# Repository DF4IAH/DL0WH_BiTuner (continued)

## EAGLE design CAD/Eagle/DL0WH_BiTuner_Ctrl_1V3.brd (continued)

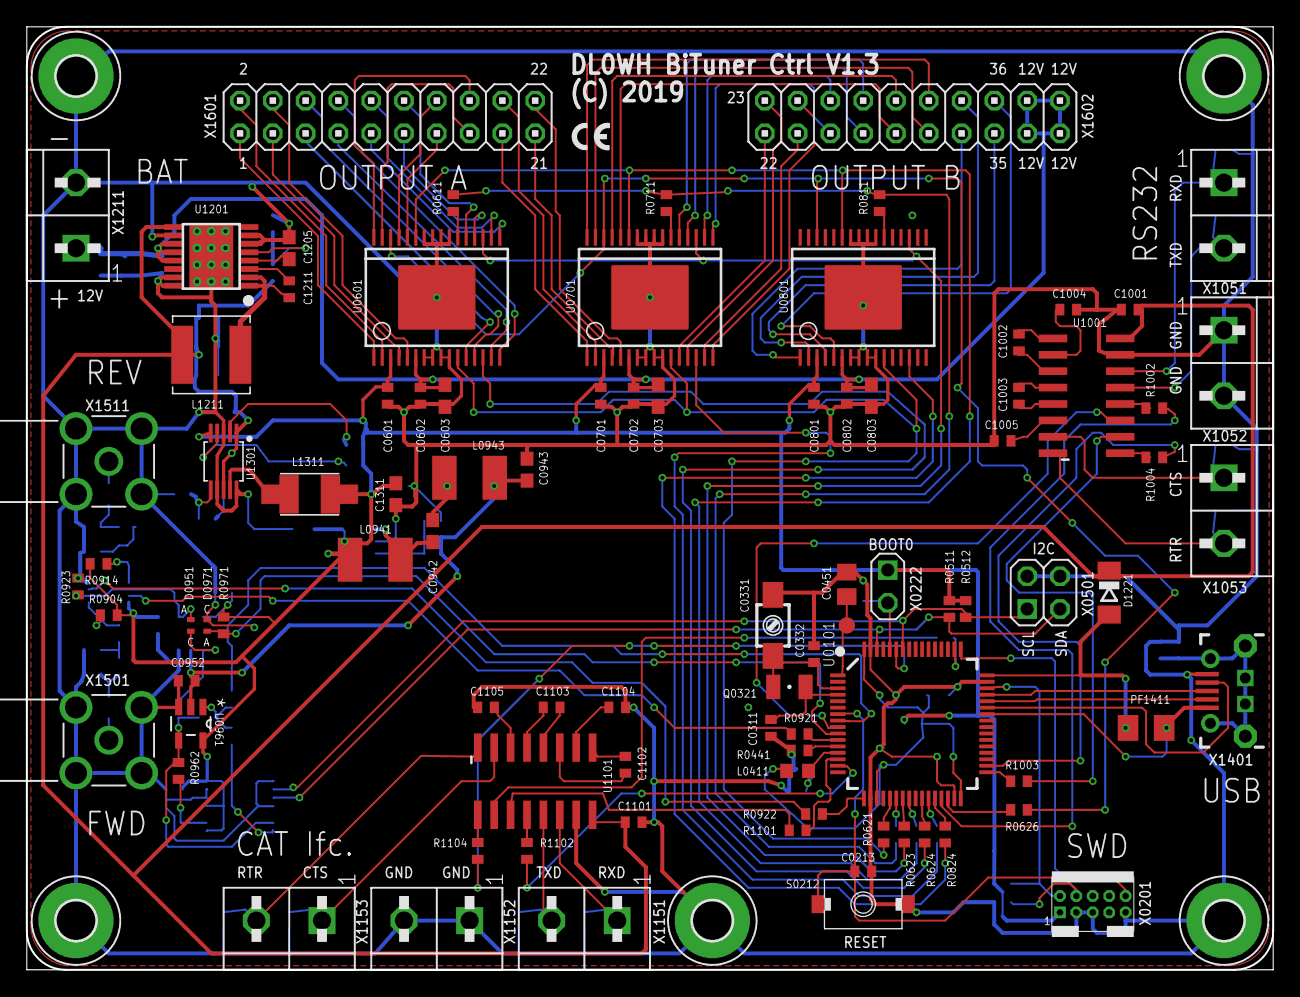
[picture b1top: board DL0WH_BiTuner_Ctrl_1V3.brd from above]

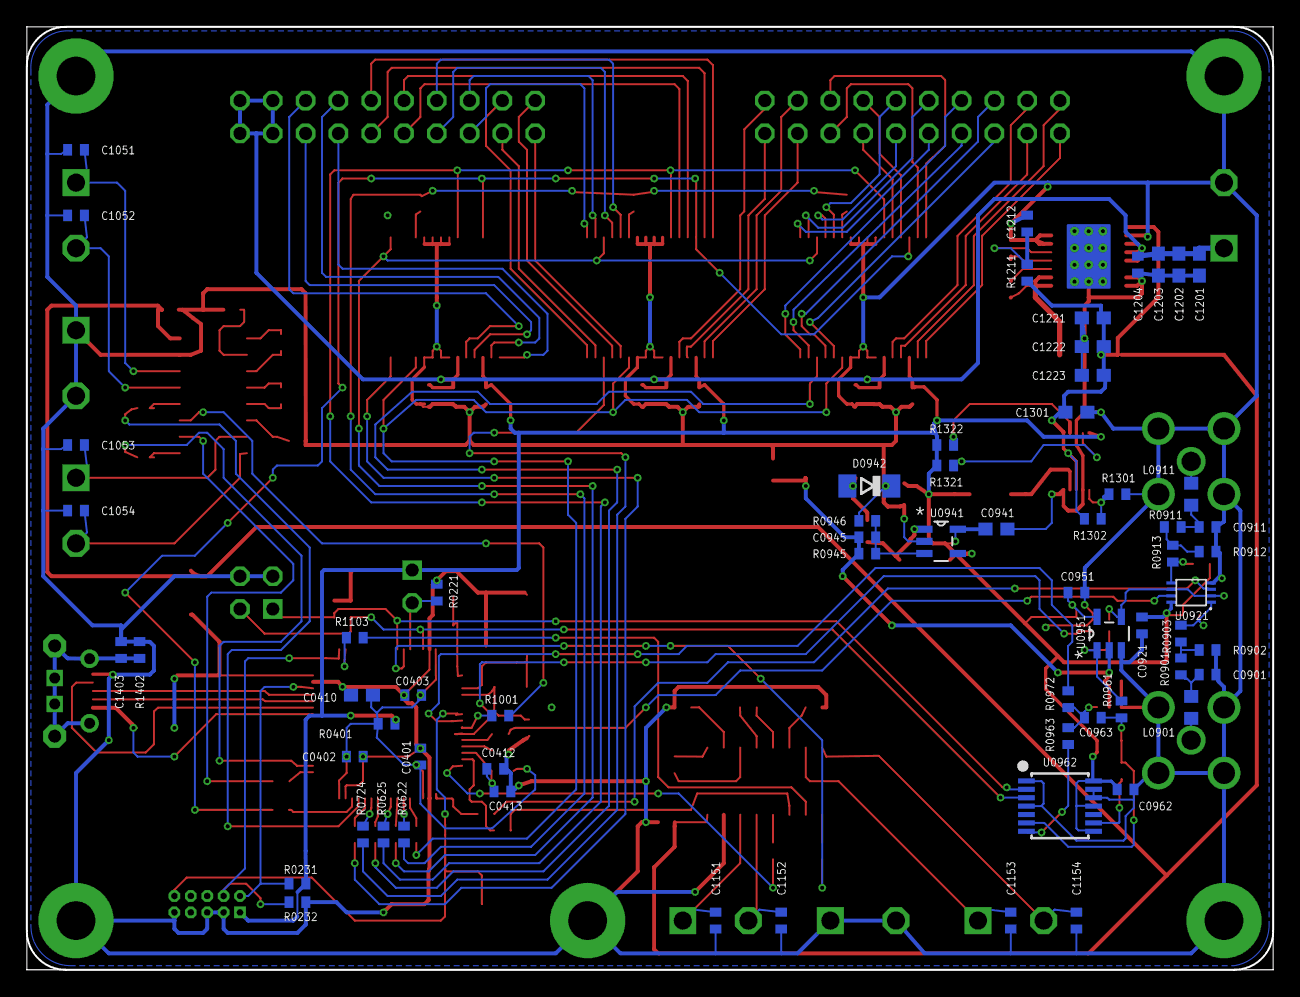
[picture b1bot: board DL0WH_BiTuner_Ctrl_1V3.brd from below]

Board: 2 copper layers, 96.5 x 73.0 mm, 160 parts (65 on the bottom side), 145 nets.

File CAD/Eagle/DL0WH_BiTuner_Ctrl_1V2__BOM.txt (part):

Stückliste exportiert aus /Users/espero/nfs_ds_nfs/git/_untracked/DL0WH_BiTuner/CAD/Eagle/DL0WH_BiTuner_Ctrl_1V2.sch am 19.04.19 14:24

Qty Value                    Device                               Package                             Parts                                                                                                                                             Description                                           

1   STM32L476RXT_64PIN_LDO   STM32L476RXT_64PIN_LDO               LQFP64                              U0101                                                                                                                                             STM32L476RxT 64LQFP                                   

2   MAX232_SOIC16            MAX232_SOIC16                        SOIC16N                             U1001, U1101                                                                                                                                      RS232 TRANSCEIVER                                     

1   LM53603-Q1               LM53603-Q1                           HTSSOP16                            U1201                                                                                                                                             TI LM53603-Q1                                         
1   TPS62056                 TPS62051                             S-PDSO-G10                          U1301                                                                                                                                             TPS62051 800-mA Synchronous Step-Down Converter: 3.3V 
1   LM2611                   LM2611                               SOT95P280X145-5N                    U0941                                                                                                                                             IC REG CUK INV ADJ 1.2A SOT23-5                       

2   OPA354                   OPA354                               SOT-23-5                            U0951, U0961                                                                                                                                      CMOS OPERATIONAL AMPLIFIERS                           

3   MC33996                  MC33996                              SOICW32                             U0601, U0701, U0801                                                                                                                               NXP MC33996                                           

1   TS5A23166                TS5A23166                            R-PDSO-G8                           U0921                                                                                                                                             TS5A23166                                             

1   MCP4661-103E-MS          MCP4661-104E-MS                      TSSOP14                             U0962                                                                                                                                             Microchip MCP4661                                     

1   ABS07-32.768KHZ          ABS07-32.768KHZ                      ABS07                               Q0321                                                                                                                                             ABRACON ABS07                                         

2   CMAD6001                 D_SOD923                             SOD923                              D0951, D0971                                                                                                                                      DIODE with SOD923 footprint                           
2   CRS08                    CRS08                                SOD80C                              D0942, D1221                                                                                                                                      SCHOTTKY BARRIER RECTIFIER                            


2   0R                       R-EU_R0402                           R0402                               R0441, R0622                                                                                                                                      RESISTOR, European symbol                             
1   3R                       R-EU_R0402                           R0402                               R1211                                                                                                                                             RESISTOR, European symbol                             
21  47R                      R-EU_R0402                           R0402                               R0611, R0621, R0623, R0624, R0625, R0626, R0711, R0724, R0811, R0824, R0921, R0922, R0972, R1001, R1002, R1003, R1004, R1101, R1102, R1103, R1104 RESISTOR, European symbol                             
6   1kR                      R-EU_R0402                           R0402                               R0511, R0512, R0901, R0911, R0961, R0962                                                                                                          RESISTOR, European symbol                             
2   2kR                      L-EUL0603                            L0603                               L0901, L0911                                                                                                                                      INDUCTOR, European symbol                             
1   8.2kR                    R-EU_R0402                           R0402                               R0945                                                                                                                                             RESISTOR, European symbol                             
1   10kR                     R-EU_R0402                           R0402                               R0971                                                                                                                                             RESISTOR, European symbol                             
2   15kR                     R-EU_R0402                           R0402                               R0902, R0912                                                                                                                                      RESISTOR, European symbol                             
1   20kR                     R-EU_R0402                           R0402                               R0963                                                                                                                                             RESISTOR, European symbol                             
2   33kR                     R-EU_R0402                           R0402                               R0221, R0946                                                                                                                                      RESISTOR, European symbol                             
1   100kR                    R-EU_R0402                           R0402                               R1301                                                                                                                                             RESISTOR, European symbol                             
2   150kR                    R-EU_R0402                           R0402                               R0903, R0913                                                                                                                                      RESISTOR, European symbol                             
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
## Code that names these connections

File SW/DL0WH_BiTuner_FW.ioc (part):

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Mcu.Name=STM32L476R(C-E-G)Tx
Mcu.Package=LQFP64
Mcu.UserName=STM32L476RGTx
PA0.GPIOParameters=GPIO_Speed
PA0.GPIO_Speed=GPIO_SPEED_FREQ_MEDIUM
PA0.Mode=Asynchronous
PA0.Signal=UART4_TX
PA1.GPIOParameters=GPIO_Speed,GPIO_PuPd
PA1.GPIO_PuPd=GPIO_PULLUP
PA1.GPIO_Speed=GPIO_SPEED_FREQ_MEDIUM
PA1.Mode=Asynchronous
PA1.Signal=UART4_RX
PA10.Mode=OTG/Dual_Role_Device
PA10.Signal=USB_OTG_FS_ID
PA11.Mode=OTG/Dual_Role_Device
PA11.Signal=USB_OTG_FS_DM
PA12.Mode=OTG/Dual_Role_Device
PA12.Signal=USB_OTG_FS_DP
PA13\ (JTMS-SWDIO).Signal=SYS_JTMS-SWDIO
PA14\ (JTCK-SWCLK).Signal=SYS_JTCK-SWCLK
PA15\ (JTDI).GPIOParameters=GPIO_Speed
PA15\ (JTDI).GPIO_Speed=GPIO_SPEED_FREQ_MEDIUM
PA15\ (JTDI).Mode=CTS_RTS
PA15\ (JTDI).Signal=UART4_RTS
PA2.Mode=SYS_WakeUp3
PA2.Signal=SYS_WKUP4
PA3.GPIOParameters=GPIO_Label
PA3.GPIO_Label=GPIO_SWR_SEL_REV
PA3.Signal=GPIO_Output
PA4.Signal=COMP_DAC11_group
PA5.Mode=Full_Duplex_Master
PA5.Signal=SPI1_SCK
PA6.GPIOParameters=GPIO_PuPd
PA6.GPIO_PuPd=GPIO_PULLDOWN
PA6.Mode=Full_Duplex_Master
PA6.Signal=SPI1_MISO
PA7.Mode=Full_Duplex_Master
PA7.Signal=SPI1_MOSI
PA8.Mode=Activate_SOF_FS
PA8.Signal=USB_OTG_FS_SOF
PA9.Mode=Activate_VBUS
PA9.Signal=USB_OTG_FS_VBUS
PB0.GPIOParameters=GPIO_Speed,PinState,GPIO_Label
PB0.GPIO_Label=GPIO_SPI_SEL_L
PB0.GPIO_Speed=GPIO_SPEED_FREQ_VERY_HIGH
PB0.PinState=GPIO_PIN_SET
PB0.Signal=GPIO_Output
PB1.GPIOParameters=GPIO_Speed,PinState,GPIO_Label
PB1.GPIO_Label=GPIO_SPI_SEL_C
PB1.GPIO_Speed=GPIO_SPEED_FREQ_VERY_HIGH
PB1.PinState=GPIO_PIN_SET
PB1.Signal=GPIO_Output
PB10.GPIOParameters=GPIO_Speed,GPIO_PuPd
PB10.GPIO_PuPd=GPIO_PULLUP
PB10.GPIO_Speed=GPIO_SPEED_FREQ_MEDIUM
PB10.Mode=Asynchronous
PB10.Signal=LPUART1_RX
PB11.GPIOParameters=GPIO_Label
PB11.GPIO_Label=GPIO_SPI_PWM
PB11.Signal=GPIO_Output
PB12.GPIOParameters=GPIO_Speed
PB12.GPIO_Speed=GPIO_SPEED_FREQ_MEDIUM
PB12.Mode=CTS_RTS
PB12.Signal=LPUART1_RTS
PB13.GPIOParameters=GPIO_Speed,GPIO_PuPd
PB13.GPIO_PuPd=GPIO_PULLUP
PB13.GPIO_Speed=GPIO_SPEED_FREQ_MEDIUM
PB13.Mode=CTS_RTS
PB13.Signal=LPUART1_CTS
PB2.GPIOParameters=GPIO_Speed,PinState,GPIO_Label
PB2.GPIO_Label=GPIO_SPI_SEL_EXT
PB2.GPIO_Speed=GPIO_SPEED_FREQ_VERY_HIGH
PB2.PinState=GPIO_PIN_SET
PB2.Signal=GPIO_Output
PB4\ (NJTRST).Mode=INP
PB4\ (NJTRST).Signal=COMP2_INP
PB6.Mode=I2C
PB6.Signal=I2C1_SCL
PB7.GPIOParameters=GPIO_Speed,GPIO_PuPd
PB7.GPIO_PuPd=GPIO_PULLUP
PB7.GPIO_Speed=GPIO_SPEED_FREQ_MEDIUM
PB7.Mode=CTS_RTS
PB7.Signal=UART4_CTS
PB9.Mode=I2C
PB9.Signal=I2C1_SDA
PC0.Signal=ADCx_IN1
PC1.GPIOParameters=GPIO_Speed
PC1.GPIO_Speed=GPIO_SPEED_FREQ_MEDIUM
PC1.Mode=Asynchronous
PC1.Signal=LPUART1_TX
PC13.Mode=Timestamp enabled
PC13.Signal=RTC_TS
PC14-OSC32_IN\ (PC14).Mode=LSE-External-Oscillator
PC14-OSC32_IN\ (PC14).Signal=RCC_OSC32_IN
PC15-OSC32_OUT\ (PC15).Mode=LSE-External-Oscillator
PC15-OSC32_OUT\ (PC15).Signal=RCC_OSC32_OUT
PC2.Signal=ADCx_IN3
PC3.GPIOParameters=GPIO_Label
PC3.GPIO_Label=GPIO_SWR_SEL_FWD
PC3.Signal=GPIO_Output
PC4.GPIOParameters=GPIO_Label
PC4.GPIO_Label=GPIO_SPI_RST
PC4.Signal=GPIO_Output
PC5.Mode=INP
PC5.Signal=COMP1_INP
PH0-OSC_IN\ (PH0).Mode=HSE-External-Oscillator
PH0-OSC_IN\ (PH0).Signal=RCC_OSC_IN
PH1-OSC_OUT\ (PH1).Mode=HSE-External-Oscillator
PH1-OSC_OUT\ (PH1).Signal=RCC_OSC_OUT
RCC.HSE_VALUE=8000000
RCC.SYSCLKFreq_VALUE=16000000
RCC.SYSCLKSource=RCC_SYSCLKSOURCE_HSI
board=custom

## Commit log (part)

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2018-12-13 README.md - explain intension of this modified FW
2018-12-13 Initial import of re-worked sources to compile with AtmelStudio 7
2018-12-13 Renaming of the sources to clearly disconnect from the DJ0ABR firmware
2018-12-13 .vs - is this directory important to include?
2018-12-29 Readout of DJ0ARB ATmega88 for security reasons (FLASH & EEPROM)
2018-12-29 No debug mode available - do not use SPI and debugWIRE together!
2018-12-30 Refactor project
2018-12-30 HW_1V0 - CAD/Eagle - Copy template from HFT-Core-Module
2018-12-30 HW_1V0 - CAD/Eagle - STM32L476RGT6 added to df4iah_stm32l4.lbr
2018-12-31 HW_1V0 - CAD/Eagle - I/O drivers added
2018-12-31 HW_1V0 - CAD/Eagle - level shifter not needed and removed
2018-12-31 HW_1V0 - CAD/Eagle - I2C port expander not needed and removed
2019-01-01 HW_1V0 - CAD/Eagle - I2C port added
2019-01-01 HW_1V0 - CAD/Eagle - SWR metering added, all placed
2019-01-01 DOCS - Datasheets and more docs added
2019-01-01 HW_1V0 - CAD/Eagle - prepared BOM and adjusted some package sizes - still L9011 needs correct package
2019-01-01 HW_1V0 - CAD/Eagle - pages renumbered: 17 pages
2019-01-02 SW - move _historic firmware to SW directory
2019-01-02 HW_1V0 - text size fixed for 0603 and 0402 devices
2019-01-02 HW_1V0 - CAD/Eagle - some parts re-routed
2019-01-02 HW_1V0 - CAD/Eagle - all placed, next: ERC and DRC
2019-01-02 HW_1V0 - CAD/Eagle - missing *.dru file added
2019-01-02 HW_1V0 - CAD/Eagle - some DRC error fixed
2019-01-02 DOCS - picture of V1.0 SW MCU Pinout added
2019-01-03 HW_1V0 - CAD/Eagle - I/O protection on V24 lines added
2019-01-04 DOCS - Final PCB picture upload
2019-01-04 HW_1V0 - CAD/Eagle - Ready for V1.0 production.
2019-01-04 HW_1V0 - CAD/Eagle - Pre-view pictures of the PCB added
2019-01-04 HW_1V0 - CAD/Eagle - Prepare for README.md update
2019-01-05 DOCS - Latching relays added
2019-01-05 SW - Initial software generation from STM32CubeMX
2019-01-05 SW - Some modifications in code generation done
2019-01-05 SW - FreeRTOS tasks and pipes established
2019-01-05 SW - some code taken from HFT-Core-Module main.[c|h]
2019-01-06 SW - infrastructure from HFT-Core-Module used as template
2019-01-06 SW - MCU ADC1..3 convertion added
2019-01-10 SW - _historic - old firmware for ATmega88 adapted to new build environment with additional mods, 9600 baud.
2019-01-11 DOCS - manufacturing - pre-views of top and bottom of the PCB
2019-01-12 SW - SPI communication added
2019-01-13 SW - SWR opti algo expanded
2019-01-13 SW - SWR opti algo missing parts added
2019-01-13 SW - Tester for task_Controller auto tuner Algo added
2019-01-13 SW - Tester expanded
2019-01-13 SW - task_Controller - missing prototypes added
2019-01-13 SW - tester - step size fixed
2019-01-14 SW - tuner Algo uses real capacity and inductivity values instead of L/C count numbers due to overlapping areas
2019-01-14 SW - printf() format fixes
2019-01-15 SW - print format different for STM32L4 and Linux/Mac environment
2019-01-15 SW - SWR Algo - additional state for FSM
2019-01-15 SW - SWR Algo - VSWR simulator added
2019-01-15 SW - SWR Algo - wrong signedness fixed
2019-01-15 SW - formatting
2019-01-15 SW - Tuner Algo - logging of proved code removed
2019-01-15 SW - Tuner Algo - first test run
2019-01-16 SW - Tuner Algo - improvements made
2019-01-17 SW - Tuner Algo - more modularized
2019-01-17 HW - CAD/Eagle/lbr - STM32L4 library with bad package LQFP64 fixed, LQFP144 minor fix
2019-01-17 SW - _Tests - more Algo checks
2019-01-17 HW_1V1 - CAD/Eagle - after DRC fixes, ready for production with new STM32L476 device package.
2019-01-18 SW - Tuner Algo - refactoring
2019-01-18 SW - Tuner Algo - Half strategy to work over
2019-01-19 SW - Tuner Algo - ZeroX okay, fine tuner under test
2019-01-19 SW - Tuner Algo - fine tuner needs better pre-placement
2019-01-19 SW - _Tests - some more tweaks done
2019-01-19 SW - _Tests - working for around 1:10 --> match
2019-01-19 SW - _Tests - Ground plane impedances added
2019-01-20 SW - verified AutoTuner coded included
2019-01-20 SW - task_Controller - Welcome message to the USB console added
2019-01-27 SW - Interpreter adapted
2019-01-27 SW - Help screen update
2019-01-28 SW - task_Controller - some more interactions
2019-01-28 SW - task_UART and task_CAT added
2019-01-29 SW - task_UART - adapted for current build
2019-01-29 SW - task_CAT - copied and adapted for current build
2019-01-29 SW - task_Interpreter - warning solved
2019-02-01 DOCS - 76_SWD-connector - added
2019-02-01 HW_1V2 - df4iah_connector.lbr - SWD connector fixed
2019-02-01 DOCS - README.md - new PCB screenshots added
2019-02-01 DOCS - README.md - tidy up
2019-02-01 DOCS - 32_PMIC - docs of both used PMICs added
2019-02-01 HW_1V1 - TPS62051 changed to TPS62056
2019-02-02 HW_1V0 HW_1V1 HW_1V2 - TPS62051 changed to TPS62056
2019-02-02 SW - IWDG disabled
2019-02-03 HW_1V2 - CAD/Eagle - add CRS08 to power the 5V rail when no 12V is attached
2019-02-03 SW - SPI1 around switched fixed
2019-02-04 SW - SPI1 to 4MHz and 2nd clock phase, missing DMAs added
2019-02-04 SW - USB working when Debugger is pull/pushed
2019-02-04 SW - new frequency of 80 MHz
2019-02-05 SW - interpreter fine
2019-02-05 Docs - 76_SWD-connector - filename breaks Windows
2019-02-05 SW - task_USB - uartTx works fine with 9.600 baud together with USB CDC
2019-02-06 SW - task_Interpreter - commands Vx, Hx and Kxyz added
2019-02-06 SW - task_Interpreter - need a solution for code interleaved execution
2019-02-08 SW - interleaved fixed. Max 15W output when switching L,C,mode
2019-02-08 SW - task_UART - DMA rollover still needs a fix
2019-02-08 SW - task_Interpreter - fix-up help, restart
2019-02-09 SW - minor but many fixes
2019-02-10 SW - main.c - mainCalcFloat2IntFrac() rounding fixed
2019-02-10 SW - main.c - mainCalcFloat2IntFrac() instrumentation removed
2019-02-10 SW - device_adc - ADCs with its own timer, shorting messaging
2019-02-10 SW - device_adc - ADC fine tuning
2019-02-10 SW - device_adc - ADC2: disconnect FWD and REV path after convertion
2019-02-10 HW_1V2 - CAD/Eagle - edge connectors need more distance
2019-02-10 DOCS - 09_Results - First idea for LogAmp for V1.2
2019-02-11 DOCS - 36_OPs - OPA354 added
2019-02-11 DOCS - 44_Diodes - CMAD6001 added
2019-02-11 DOCS - 32_PMIC - TI LM2611 added for negative voltage
2019-02-11 DOCS - 55_Inductivities - 22uH 3mm x 3mm SMD1212 added
2019-02-11 DOCS - 52_Dig-POTs - 10kR 2x Poti
2019-02-11 HW_1V2 - CAD/Eagle - LogAmp added
2019-02-11 DOCS - 09_Results - LogAmp / diodes vs. temperature
2019-02-11 HW_1V2 - CAD/Eagle/df4iah_powersupply - LM2611 added
2019-02-11 HW_1V2 - CAD/Eagle - LogAmp enhanced
2019-02-11 DOCS - 09_Results - CMAD6001 metered with N=1.24 instead of N=1.43 (2)
2019-02-11 DOCS - 09_Results - CMAD6001 metered with N=1.24 instead of N=1.43 (3)
2019-02-12 HW_1V2 - CAD/Eagle/lbr - df4iah_powersupply package SOT95P280X145-5N text size fixed
2019-02-12 HW_1V2 - CAD/Eagle/lbr - df4iah_opamp package SOT-23-5 and SOT-23-6 text size fixed
2019-02-12 HW_1V2 - CAD/Eagle/lbr - df4iah_connector SWD-connector restring change
2019-02-12 HW_1V2 - CAD/Eagle - PCB V1.2 ordered
2019-02-13 HW_1V3 - CAD/Eagle/lbr - df4iah_osc, df4iah_powersupply, df4iah_sensors update
2019-02-14 SW - help system minor changes
2019-02-19 SW - Release mode fixed
2019-02-22 SW - Atollic upgrade 9.3.0 and MX update
2019-02-22 SW - new power calculations
2019-02-28 HW_1V3 - CAD/Eagle/lbr - df4iah_stm32l4.lbr STM32Ll452RE added
2019-03-01 HW_1V3 - CAD/Eagle/lbr - updates for df4iah_powersupply, df4iah_rcl and df4iah_stm32l4
2019-03-03 HW_1V3 - CAD/Eagle/lbr - df4iah_memory.lbr FRAM FEDR44V064B-02 added
2019-03-03 HW_1V3 - CAD/Eagle/lbr - df4iah_adc.lbr NAU7802 added
2019-03-03 HW_1V3 - CAD/Eagle/lbr - df4iah_connector.lbr PhoenixContact 2.5mm Wire-to-Board TermBlock added
2019-03-03 HW_1V3 - CAD/Eagle - eagle.epf update
2019-03-03 SW - Atollic environment update
2019-03-07 HW_1V3 - CAD/Eagle/lbr - df4iah_rf.lbr ESP-12F added
2019-03-09 HW_1V3 - CAD/Eagle/lbr - df4iah_rf.lbr ESP-12F pin directions fixed
2019-03-14 HW_1V3 - CAD/Eagle - MCU name fixed
2019-03-17 HW_1V3 - CAD/Eagle - renaming fix, jumper replaced by 0R bridge
2019-03-17 SW - Update of STM32CubeMX to V5.1.0
2019-03-18 HW_1V3 - CAD/Eagle - PMIC CUK additional soft-start, OpAmp output w/ higher resistor
2019-03-29 SW - relay init, terminal display enhanced
2019-03-30 SW - I2C1 fixed, bus scan added
2019-03-30 HW_1V3 - CAD/Eagle - I2C address of dig.poti fixed to 0x14
2019-03-30 SW - interpreter - new commands for dig.pot. added
2019-03-30 HW_1V3 - CAD/Eagle - broken wire fixed
2019-03-30 HW_1V3 - CAD/Eagle - diodes - missing A and C marks added
2019-03-30 HW_1V3 - CAD/Eagle - SMA sockets markings fixed (REV <--> FWD)
2019-03-31 SW - ADC/controller - signaling modified
2019-03-31 SW - quick and dirt solution for dig poti
2019-04-01 SW - DL0WH_BiTuner.ioc - 80MHz --> 16MHz
2019-04-01 SW - Downgrade to: MX V4.27.0, FW V1.12.0, TrueSUDIO STM32 V5.3.0 --> does work nearly complete, still some HardFaults
2019-04-01 SW - trying FW 1.13.0 and TrueSTUDIO STM32 V5.3.0 again
2019-04-01 SW - port.c - bad init fixed
2019-04-01 SW - another bug jumps wild, more introspection needed
2019-04-02 SW - task_CAT - duplicate of UART (update)
2019-04-02 SW - task_UART - type fix
2019-04-02 SW - task_Interpreter - adapted for new prototypes of task_USB and task_UART
2019-04-02 SW - task_Interpreter - made code more robust
2019-04-02 SW - task_Controller - code made more robust
2019-04-02 SW - bus_i2c - code made more robust
2019-04-02 SW - destroyed pxTCB for unknown reason, task stack sizes doubled already
2019-04-02 SW - still destroyed pxTCB after re-export for FW V1.13.0
2019-04-03 SW - DL0WH_BiTuner.ioc - trying new FreeRTOS set-up
2019-04-04 DOCS - forward until df4fd7a65716eb1a1b8dad1e9e020a2e6c04cd7f (2019-04-03)
2019-04-04 HW_1V3 - forward until df4fd7a65716eb1a1b8dad1e9e020a2e6c04cd7f (2019-04-03)
2019-04-04 SW - RtosDefault timer running at every 30ms
2019-04-04 SW - ADC start/stop and values re-organized
2019-04-06 SW - ADC2 working. For reliable 30ms period USB has to be disabled
2019-04-06 SW - ADCs calibrated
2019-04-06 SW - task_Controller - spelling (cherry: b48870203dc3e88748f9b94d8d446dfb6c681701)
2019-04-06 SW - use interpreterConsolePush (cherry: b48870203dc3e88748f9b94d8d446dfb6c681701)
2019-04-06 SW - use snprintf() instead of unsecured variant
2019-04-06 SW - task_Interpreter - fix for clear screen
2019-04-06 SW - task_Interpreter - init fix (cherry: 5b80c603c5e35eadf550d8289eeb7ec82cb53e50)
2019-04-06 SW - showCursor() added
2019-04-06 SW - new power calculations (cherry: 3ea48cbba87a3736a40f991065554441d21f3195)
2019-04-06 HW_1V3 - .gitignore - Eagle shadow files rule added (cherry: 388dc74971f7037a522aefce2066d87f859538c4)
2019-04-06 SW - missing help line fixed, all cherry-picking from previous branch done
2019-04-06 SW - I2C1 bus scan OK, addr 0x28 for DigPot. found
2019-04-06 HW_1V2 - CAD/Eagle - wrong I2C address fixed
2019-04-06 HW_1V3 - CAD/Eagle - wrong I2C address fixed
2019-04-07 SW - text change
2019-04-07 DOCS - Spice simulation - re-work for Log-Amp after voltage divider was added
2019-04-08 SW - DigPot. values adjusted to work with exp() and linear regression
2019-04-08 SW - linearity checks and tests vs. ambient temperature
2019-04-10 SW - stop UART DMA before starting again
2019-04-10 SW - relay OFF by timer event 30ms after ON signal
2019-04-11 SW - controller.c - FSM re-worked, trouble at local variable line 1494
2019-04-13 SW - controller - timing fixes
2019-04-14 SW - task_UART - eventgroup handling fixed
2019-04-14 SW - controller - algo finished, real tests to be done
2019-04-16 SW - interpreter, controller - switch for automatic matching added
2019-04-18 SW - STM32CubeMX project file - ST.com try to get a clean version of the previous V5.10 *.ioc variant
2019-04-18 SW - STM32CubeMX project file - removed again, it is not needed anymore
2019-04-19 HW_1V2,HW_1V3 - CAD/Eagle - BOM lists update
2019-04-20 SW - 2nd device proof - adjustments for the 2nd device
2019-04-22 SW - adc - automatic OpAmp settings and offset calibration
2019-04-22 SW - adc - fwd voltage fix
2019-04-23 SW - task_Controller - auto tuner separated into coarse and fine tuning
2019-04-25 SW - task_Controller - fine tuning complete
